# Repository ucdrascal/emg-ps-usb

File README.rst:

==========
emg-ps-usb
==========

.. image:: rev1/board.png
   :alt: Board screenshot

Description
===========
This is a power supply design for powering Motion Lab Systems Y03 or Z03 EMG
preamplifiers with a standard USB port. The board is designed to function like
a USB dongle with EMG electrode leads coming from it and a 1/8" `TS phone
connector`_ output (e.g. to connect to a computer's microphone port).

It uses a charge pump voltage converter chip to generate -5V from +5V USB
power. It is recommended that the design in the current state be used only with
USB ports belonging to devices isolated from mains earth (ground). This is
because there is no galvanic isolation between the USB port's ground and the
ground electrode, which connects directly to the user. It was originally
designed to connect to Android tablets which have a full-size USB A jack and
a TRRS headset inputs.

Parts
=====
Integrated circuits:

* `Analog Devices ADM660`_ switched-capacitor voltage converter

Electromechanical:

* Apem MA12R/TR SPDT switch
* CUI MJ-3523-SMT 3.5mmm mono phono jack
* Molex 480390001 USB-A connector
* TE Connectivity 284093-2 2x1 screw terminal block
* MyCableMart.com 6" 3.5mm mono male to male cable

Discrete components:

* Samsung CL21A106KAYNNNE 10uF ceramic capcaitor
* Panasonic ERJ-6GEYJ101V 100 Ohm thick film resistor
* Panasonic ERJ-6GEYJ102V 1k Ohm thick film resistor
* OSRAM LS L29K-G1J2-1-Z red LED

Details, including vendor links and prices are in bill-of-materials.ods.

License
=======

The contents of this repository are licensed under the `CC-BY 4.0 license`_.

.. REFERENCES
.. _`Analog Devices ADM660`: http://www.analog.com/en/power-management/switched-capacitor-converters/adm660/products/product.html
.. _`TS phone connector`: https://en.wikipedia.org/wiki/Phone_connector_(audio)
.. _`CC-BY 4.0 license`: https://creativecommons.org/licenses/by/4.0/

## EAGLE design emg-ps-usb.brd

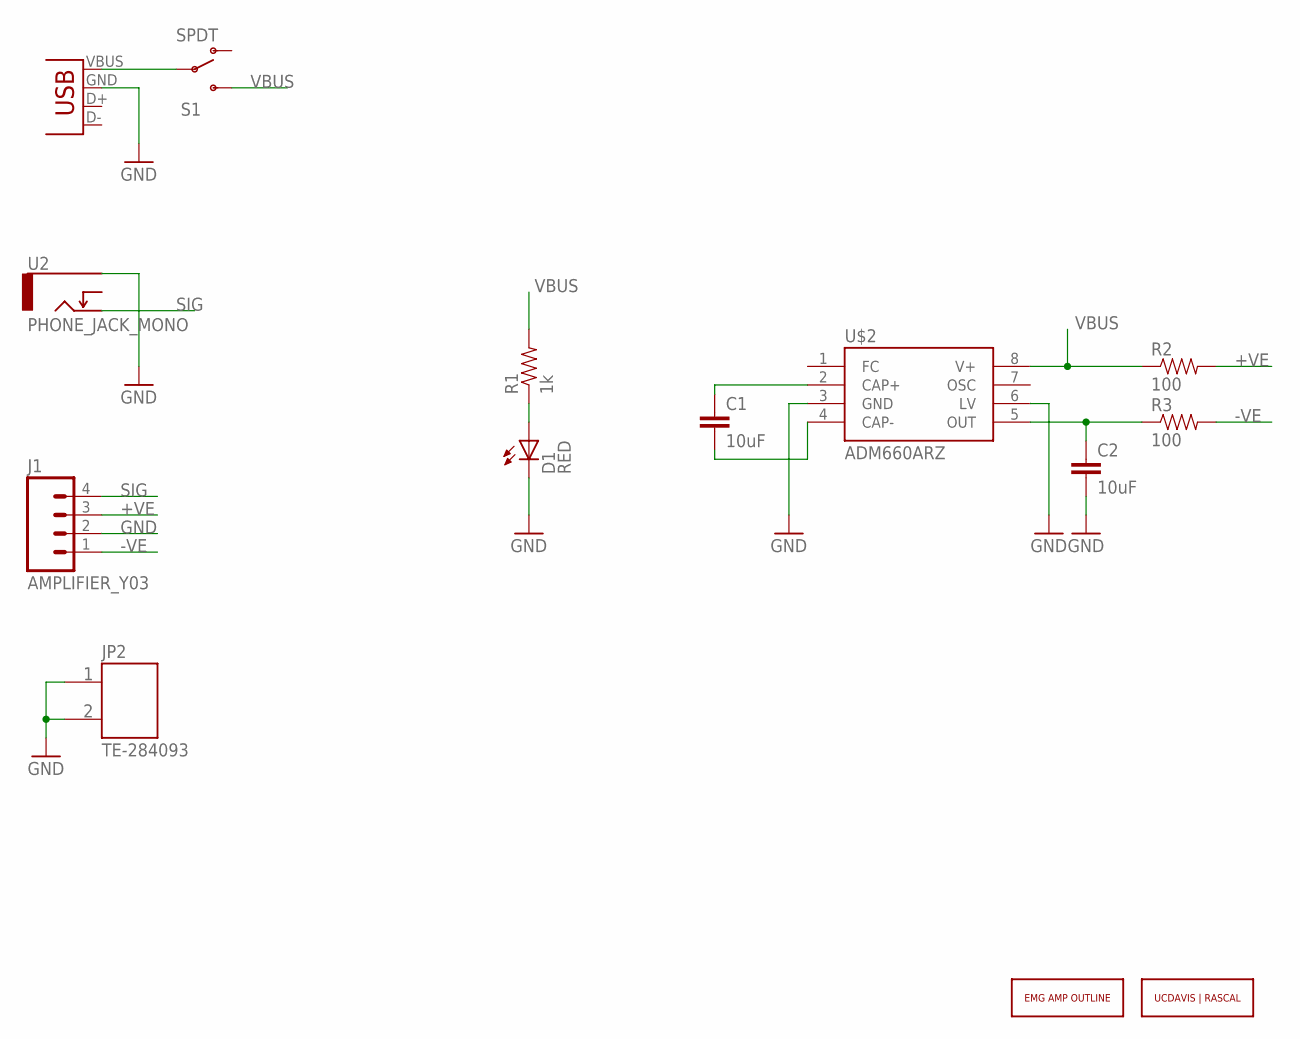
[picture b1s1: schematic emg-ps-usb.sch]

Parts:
C1, C2: 10uF; 0805
D1: RED; LED-0603
J1: AMPLIFIER_Y03; AMPLIFIER_WTB
JP1: USB-A-H
JP2: TE-284093
R1: 1k; 0805
R2, R3: 100; 0805
S1: SPDT; SWITCH-SPST-SMD-A
U2: PHONE_JACK_MONO; MJ-3523-SMT
U$1: UCDAVIS-RASCAL_LOGO-2LINE; UCDAVIS-RASCAL_LOGO
U$2: ADM660ARZ; SOIC8
U$3: EMG_AMP_OUTLINE-Y03ENDS; EMG_Y03_OUTLINEENDS

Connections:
+VE: J1.3, R2.2
-VE: J1.1, R3.2
GND: C2.2, D1.C, J1.2, JP1.GND (VBUS), JP2.P$1 (1), JP2.P$2 (2), U2.P$1, U$2.3 (GND), U$2.6 (LV)
unnamed: JP1.VBUS (GND), S1.2
unnamed: D1.A, R1.1
unnamed: C2.1, R3.1, U$2.5 (OUT)
unnamed: C1.2, U$2.4 (CAP-)
unnamed: C1.1, U$2.2 (CAP+)
SIG: J1.4, U2.P$2
VBUS: R1.2, R2.1, S1.3 (S), U$2.8 (V+)

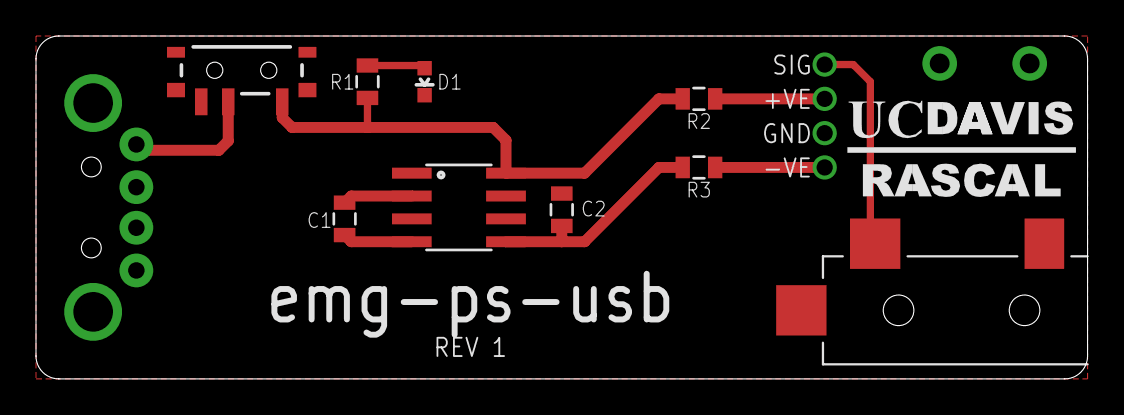
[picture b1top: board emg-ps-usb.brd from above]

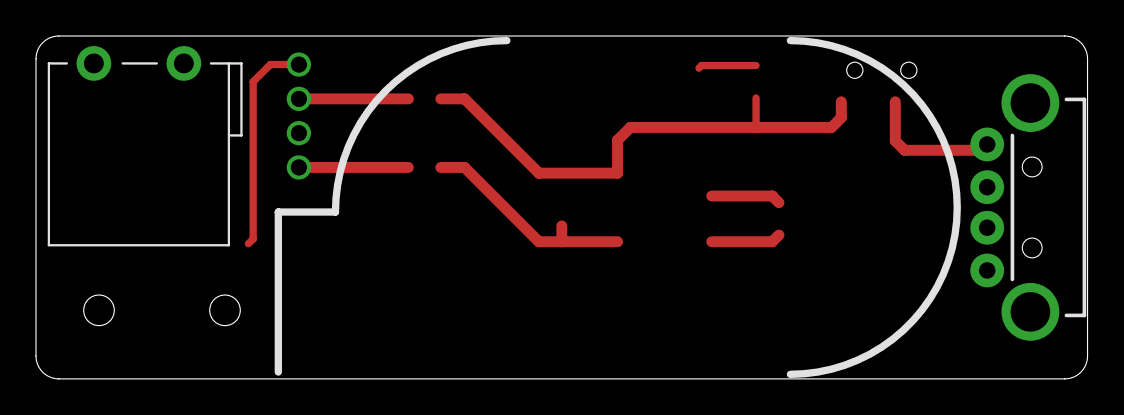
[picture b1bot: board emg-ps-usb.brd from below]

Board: 2 copper layers, 58.4 x 19.1 mm, 14 parts (3 on the bottom side), 10 nets.

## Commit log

2013-09-29 Initial commit. Board is essentially done but needs thorough review.
2013-09-29 Cleaned up schematic and added a frame.
2013-09-29 Added labels to the EMG amp connector. Decreased size of component names.
2013-09-29 Now using EMG amp outline and UCDAVIS|RASCAL logo from ucdrascal-eagle-lib.
2013-09-29 Refreshed library parts (UCDAVIS|RASCAL logo).
2013-09-30 Shifted some component labels to get them out of tStop.
2014-01-13 Cleaned up layout and routing. Moved LED to top and removed UCDRASCAL logo.
2014-02-12 Added UCDRASCAL logo. Swapped the 4x1 Molex connector for just a wire to board interface. Updated BOM.
2014-02-12 Forgot to update README on previous commit.
2014-02-13 Added pad labels on amplifier side. Ordered the board and copied to rev1 subfolder.
2018-02-12 Added screenshot of board to README.
2018-02-12 Updated README.
2018-02-12 Added LICENSE.

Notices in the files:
parts and their libraries:
SparkFun-Connectors: Licensing: CC v3.0 Share-Alike You are welcome to use this library for commercial purposes.
